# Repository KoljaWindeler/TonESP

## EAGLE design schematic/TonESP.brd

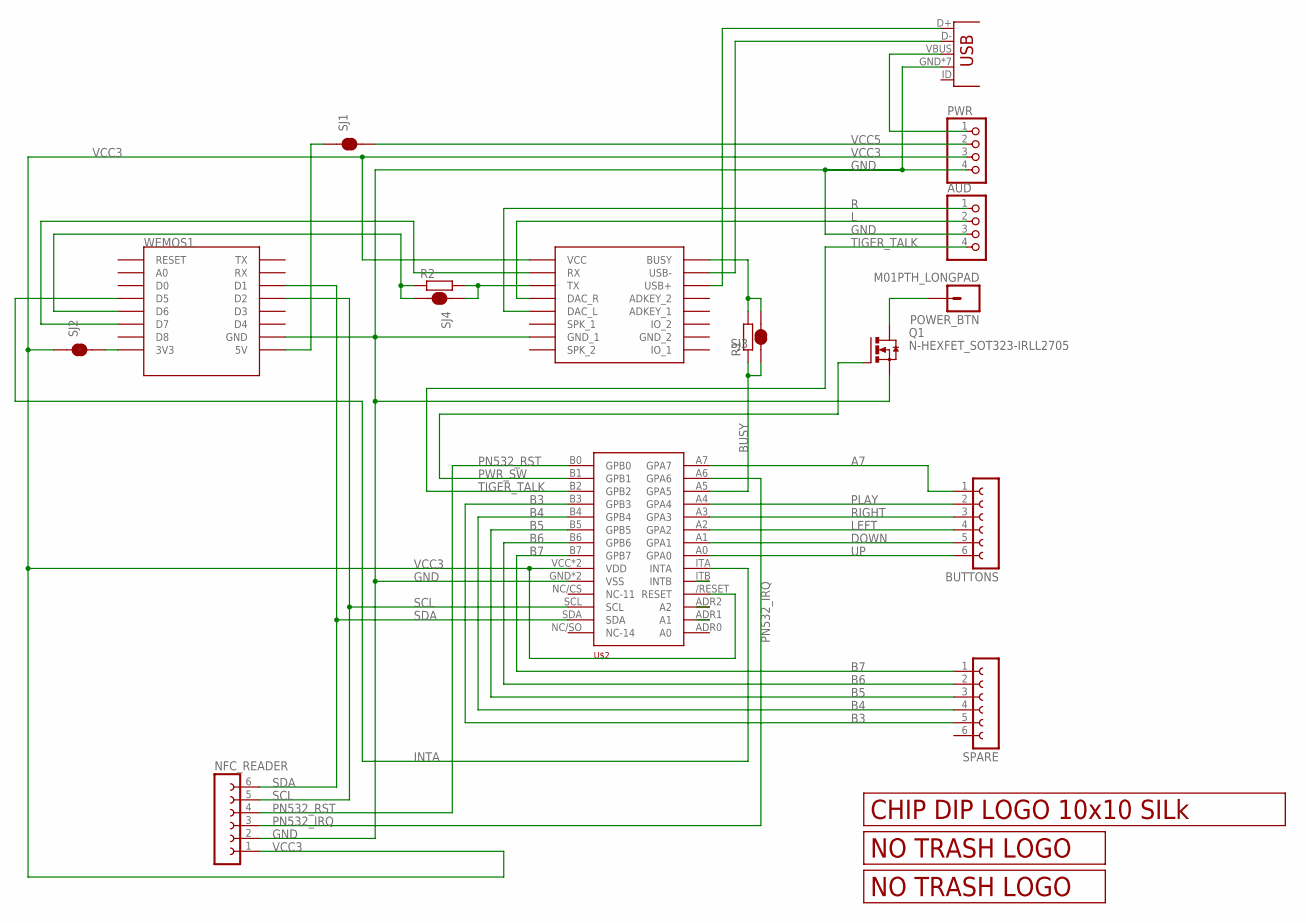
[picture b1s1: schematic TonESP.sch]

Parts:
AUD: PINHD-1X4; 1X04
BUTTONS: FE06-1; FE06
JP1: USBUSB-MICROB-SMT-DIP; USB-MICROB-SMT-DIP
NFC_READER: FE06-1; FE06
POWER_BTN: M01PTH_LONGPAD; 1X01_LONGPAD
PWR: PINHD-1X4; 1X04
Q1: N-HEXFET_SOT323-IRLL2705; SOT223
R1, R2: R-EU_M0805; M0805
SJ1, SJ3, SJ4: SMD_SJ_2WAY_CLOSEDCLOSED; SMD_SJ_2WAY_CLOSED
SJ2: SMD_SJ_2WAY_OPEN
SPARE: FE06-1; FE06
U$1: DFPLAYER
U$2: MCP23017-E/SP; MODULE
U$4: LOGO_10X10_SILK; LOGO2_10X10_SILK
U$5: LOGO_NO_TRASHNO_TRASH; LOGO_ROHS_NO_TRASH
U$6: LOGO_NO_TRASHROHS; LOGO_ROHS_SYM
WEMOS1: WEMOS-D1-MINITXT; WEMOS-D1-MINI

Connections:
A7: BUTTONS.1, U$2.A7 (GPA7)
B3: SPARE.5, U$2.B3 (GPB3)
B4: SPARE.4, U$2.B4 (GPB4)
B5: SPARE.3, U$2.B5 (GPB5)
B6: SPARE.2, U$2.B6 (GPB6)
B7: SPARE.1, U$2.B7 (GPB7)
BUSY: R1.1, SJ3.1, U$2.A5 (GPA5)
DOWN: BUTTONS.5, U$2.A1 (GPA1)
GND: AUD.3, JP1.GND, JP1.MT1 (GND), JP1.MT2 (GND), JP1.MT3 (GND), JP1.MT4 (GND), JP1.P$1 (GND), JP1.P$2 (GND), NFC_READER.2, PWR.4, Q1.3 (S), U$1.GND_1, U$2.GND (VSS), U$2.GND2 (VSS), WEMOS1.GND
INTA: U$2.ITA (INTA), WEMOS1.D5
L: AUD.2, U$1.DAC_R
LEFT: BUTTONS.4, U$2.A2 (GPA2)
unnamed: SJ2.3, WEMOS1.3V3
unnamed: SJ1.1, WEMOS1.5V
unnamed: R1.2, SJ3.3, U$1.BUSY
unnamed: R2.2, SJ4.1, U$1.TX
unnamed: R2.1, SJ4.3, WEMOS1.D6
unnamed: U$1.RX, WEMOS1.D7
unnamed: POWER_BTN.1, Q1.4 (D)
unnamed: JP1.VBUS, PWR.1
unnamed: JP1.D-, U$1.USB-
unnamed: JP1.D+, U$1.USB+
PLAY: BUTTONS.2, U$2.A4 (GPA4)
PN532_IRQ: NFC_READER.3, U$2.A6 (GPA6)
PN532_RST: NFC_READER.4, U$2.B0 (GPB0)
PWR_SW: Q1.1 (G), U$2.B1 (GPB1)
R: AUD.1, U$1.DAC_L
RIGHT: BUTTONS.3, U$2.A3 (GPA3)
SCL: NFC_READER.5, U$2.SCL, WEMOS1.D2
SDA: NFC_READER.6, U$2.SDA, WEMOS1.D1
TIGER_TALK: AUD.4, U$2.B2 (GPB2)
UP: BUTTONS.6, U$2.A0 (GPA0)
VCC3: NFC_READER.1, PWR.3, SJ2.1, U$1.VCC, U$2./RESET (RESET), U$2.VCC (VDD), U$2.VCC2 (VDD)
VCC5: PWR.2, SJ1.3

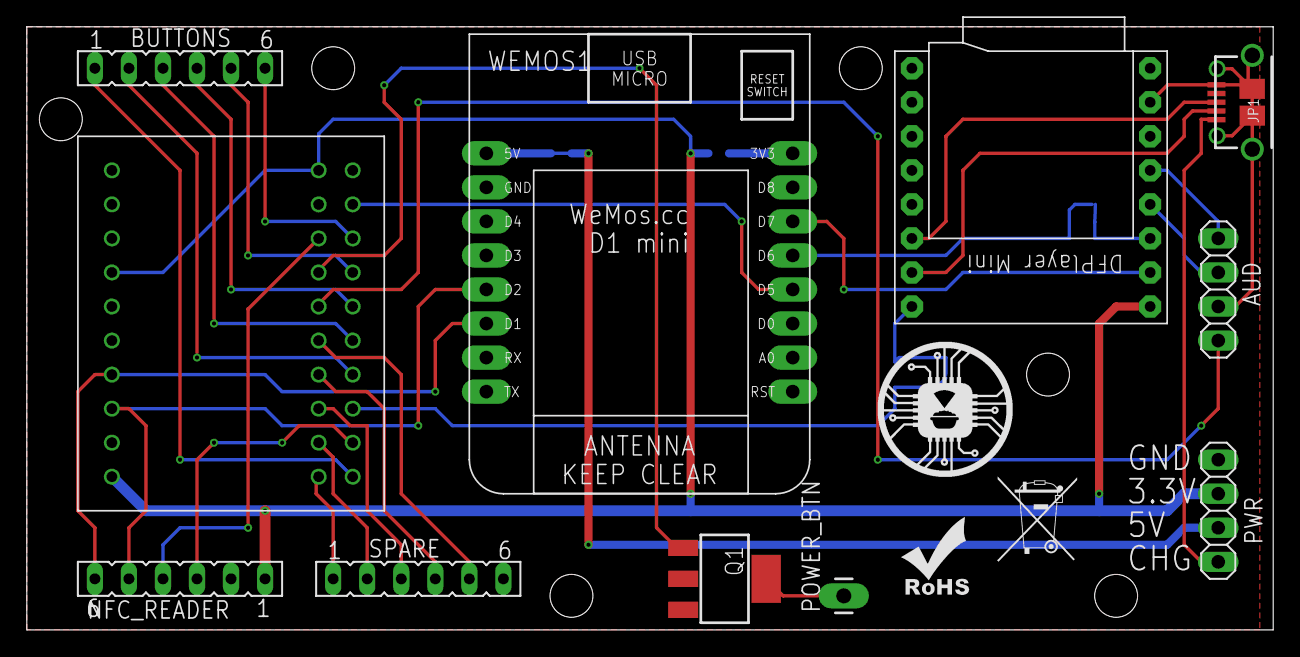
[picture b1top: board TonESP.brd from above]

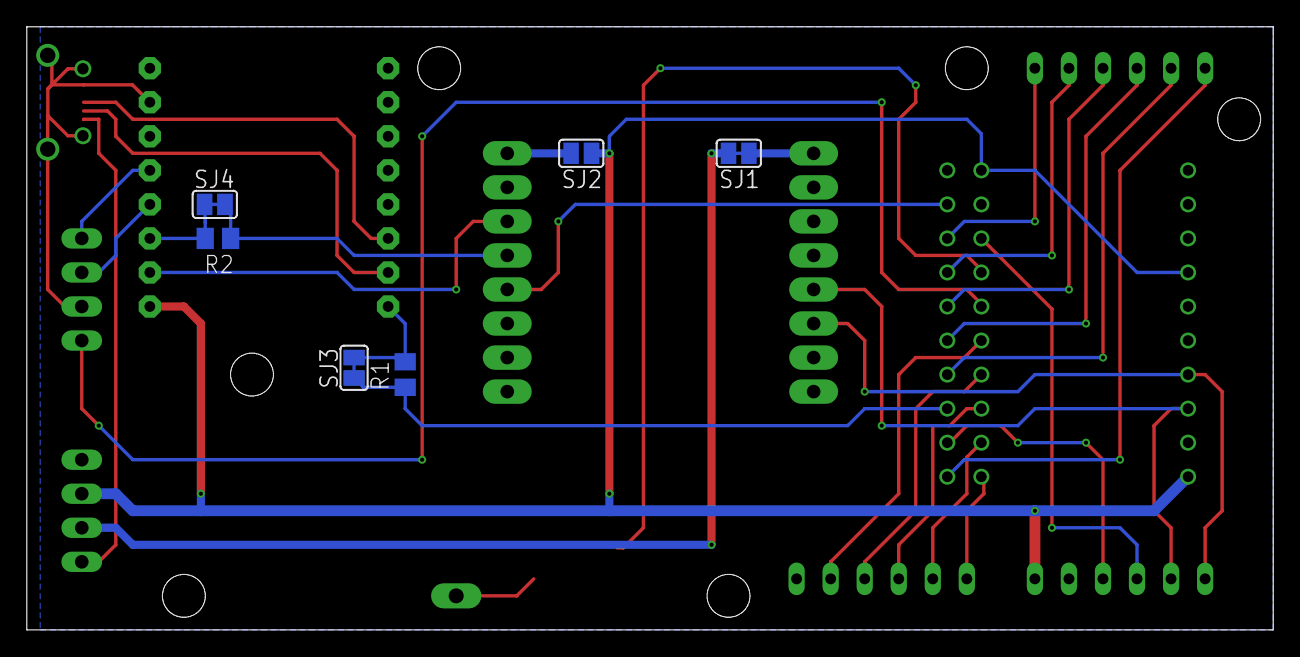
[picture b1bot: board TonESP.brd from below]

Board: 2 copper layers, 93.0 x 45.0 mm, 20 parts (6 on the bottom side), 34 nets.

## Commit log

2019-02-03 init
2019-02-05 port extender working, no SD comm check?
2019-02-08 somewhat stable card read, although I don't like the 1sec timeout
2019-02-09 fixed loading function, added get pointer to read write on member vars :/
2019-02-09 menu somewhat working
2019-02-09 removed compiler warnings
2019-02-09 moved mp3 specific vars to class
2019-02-10 changed to 16 bit
2019-02-10 merged next/prev/init to one play function
2019-02-10 updated gitignore to keep the default sdkard files
2019-02-10 added espserial lib
2019-02-10 moved lib
2019-02-10 moved lib2
2019-02-11 somewhat stable, wifi working, MQTT working
2019-02-12 beautified log output
2019-02-13 added wifi update and log colorisation
2019-02-13 added libs
2019-02-13 add google voice + carlo + wifi mp3
2019-02-13 add new mp3 files
2019-02-13 renamed card files
2019-02-13 wifi states as define, load card only if needed, faster
2019-02-13 removed old style debug
2019-02-13 smarter way to prgramm the wait for mp3 data
2019-02-13 gpio state needed as global (wifi)
2019-02-13 invert polarity for busy pin
2019-02-13 added support of lock mode
2019-02-13 debug formarting
2019-02-13 next and prev not available during setup
2019-02-14 increased buffer size for userdata
2019-02-14 added userdata
2019-02-14 moved pins t dedicated port
2019-02-14 publish card_found instead of search to publish e.g. user_data as well
2019-02-14 initial version
2019-02-14 adding more ignore files to get ridge of all the temp files
2019-02-15 implemented power down - after track - after time - after idle time
2019-02-15 formating
2019-02-15 avoid menu playing of new card in lock mode
2019-02-15 clorized setting output
2019-02-15 move credential to dedicated file
2019-03-03 publish some states
2019-03-03 add detail level of dump
2019-03-03 changedfrom up anddownto left andright
2019-03-03 updated schematics, added backup text file
2019-03-03 added layout files
2019-03-03 updated ignore files, for backup files
2019-03-03 Updated advert tracks

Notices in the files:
parts and their libraries:
JKW_CHIP: License : http://creativecommons.org/licenses/by-sa/3.0
(Creative Commons 3.0)
SparkFun: Licensing: CC v3.0 Share-Alike You are welcome to use this library for commercial purposes.
